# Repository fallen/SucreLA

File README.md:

# SucréLA (READ ONLY, MOVED TO GITLAB)

This is an archived, out-of-date and read-only copy of the SucréLA project.

The project is now hosted on **GitLab** => [https://gitlab.com/yannsionneau/SucreLA](https://gitlab.com/yannsionneau/SucreLA)

## Building

The project Python's dependencies are handled using Pipenv.
However, you must install [nextpnr-ecp5](https://github.com/YosysHQ/nextpnr) and [Yosys](https://github.com/YosysHQ/yosys) if you wish to build the
projet from source.

```
pipenv install --ignore-pipfile
pipenv run python3 ./sucrela.py --build
```

## Flashing the OrangeCrab

```
pipenv run python3 ./sucrela.py --load
```

## Runing simulation

```
pipenv run python3 ./sucrela.py --sim
```

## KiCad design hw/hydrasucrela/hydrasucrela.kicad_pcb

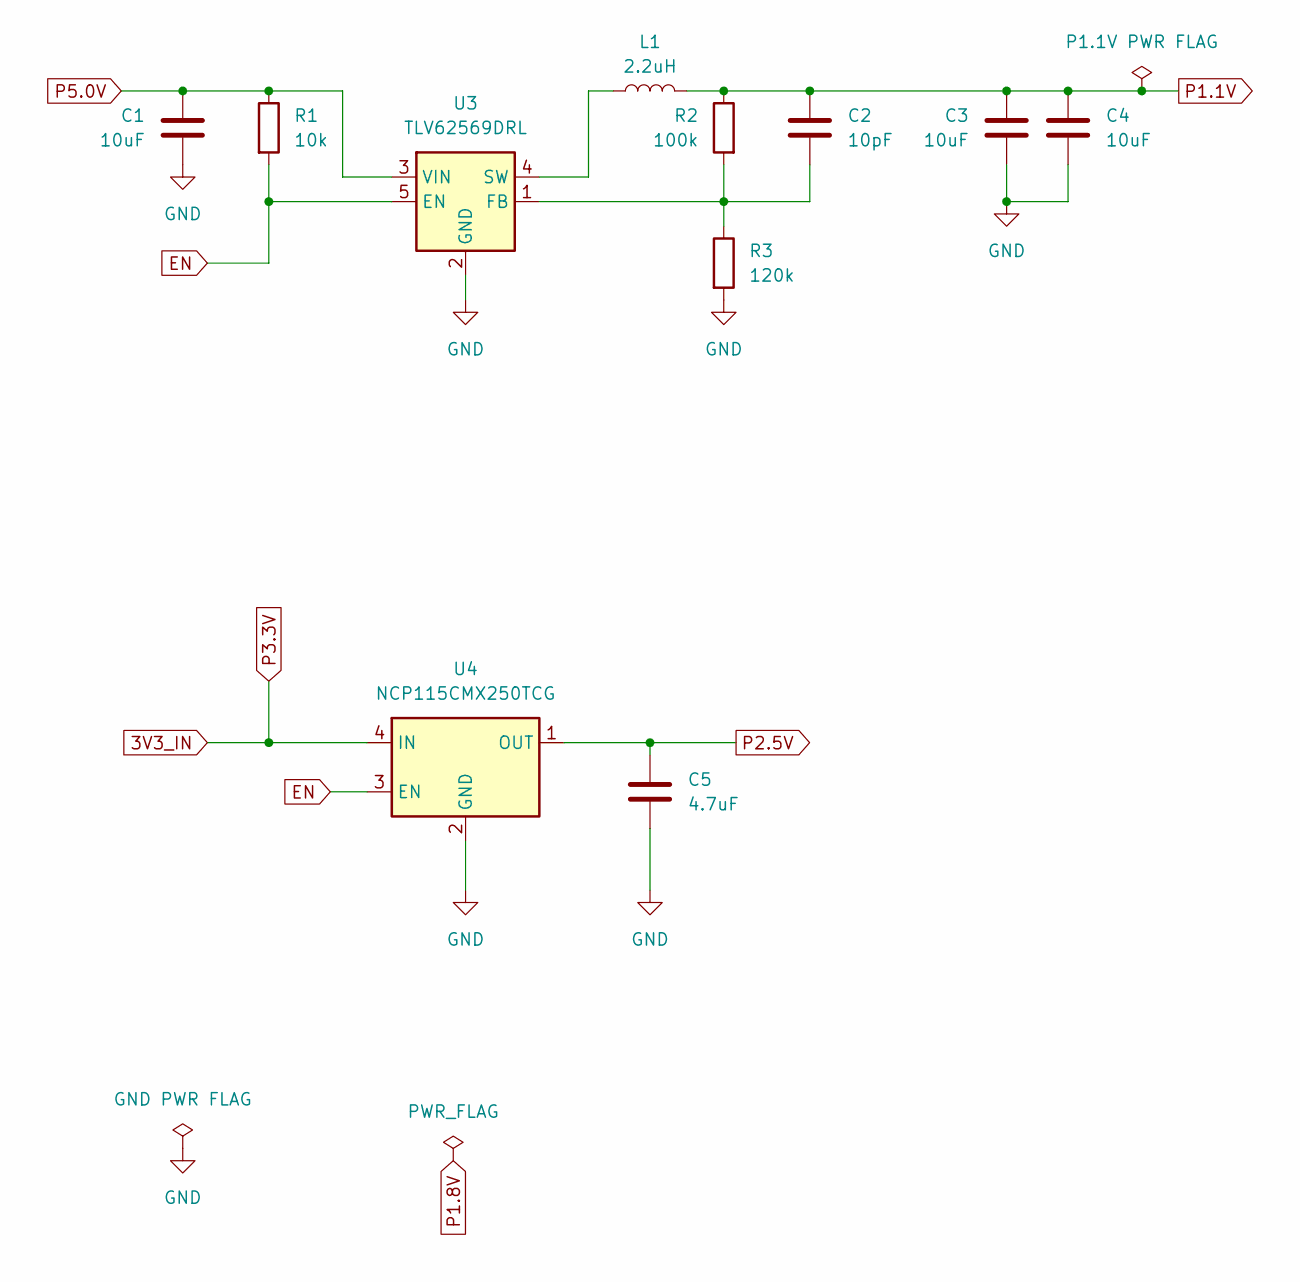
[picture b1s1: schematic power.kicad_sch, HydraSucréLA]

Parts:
C1, C3, C4: 10uF; C_0603_1608Metric_Pad1.08x0.95mm_HandSolder
C2: 10pF; C_0603_1608Metric_Pad1.08x0.95mm_HandSolder
C5: 4.7uF; C_0603_1608Metric_Pad1.08x0.95mm_HandSolder
L1: 2.2uH; L_0603_1608Metric_Pad1.05x0.95mm_HandSolder
R1: 10k; R_0603_1608Metric_Pad0.98x0.95mm_HandSolder
R2: 100k; R_0603_1608Metric_Pad0.98x0.95mm_HandSolder
R3: 120k; R_0603_1608Metric_Pad0.98x0.95mm_HandSolder
U3: TLV62569DRL; SOT-563
U4: NCP115CMX250TCG; OnSemi_XDFN4-1EP_1.0x1.0mm_EP0.52x0.52mm

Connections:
3V3_IN: U4.4 (IN); also elsewhere on the board
EN: R1.2, U3.5 (EN), U4.3 (EN)
GND: C1.2, C3.1, C4.1, C5.2, R3.2, U3.2 (GND), U4.2 (GND), U4.5 (GND); also elsewhere on the board
unnamed: C2.1, R2.2, R3.1, U3.1 (FB)
unnamed: L1.1, U3.4 (SW)
P1.1V: C2.2, C3.2, C4.2, L1.2, R2.1; also elsewhere on the board
P2.5V: C5.1, U4.1 (OUT); also elsewhere on the board
P5.0V: C1.1, R1.1, U3.3 (VIN); also elsewhere on the board

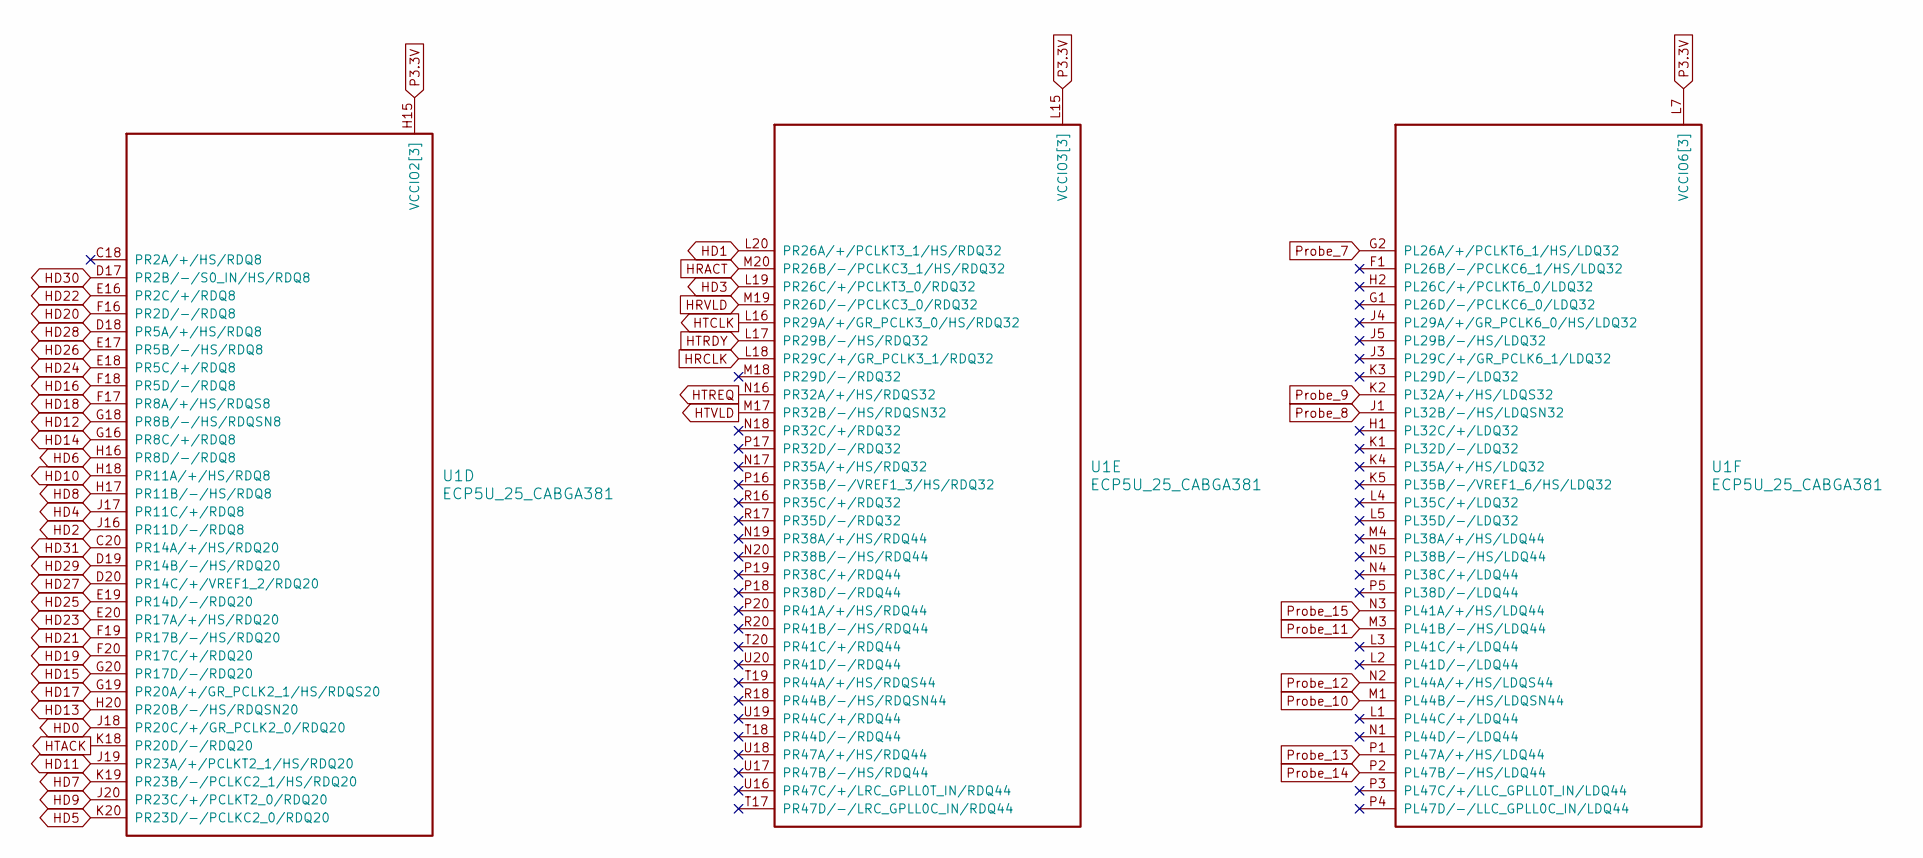
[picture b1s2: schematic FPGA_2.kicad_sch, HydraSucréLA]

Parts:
U1: ECP5U_25_CABGA381; Lattice_caBGA-381_17.0x17.0mm_Layout20x20_P0.8mm_Ball0.4mm_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

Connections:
3V3_IN: U1.H14 (VCCIO2[3]), U1.H15 (VCCIO2[3]), U1.J15 (VCCIO2[3]), U1.L6 (VCCIO6[3]), U1.L7 (VCCIO6[3]), U1.L14 (VCCIO3[3]), U1.L15 (VCCIO3[3]), U1.M6 (VCCIO6[3]), U1.M15 (VCCIO3[3]); also elsewhere on the board
HD0: U1.J18 (PR20C/+/GR_PCLK2_0/RDQ20); also elsewhere on the board
HD1: U1.L20 (PR26A/+/PCLKT3_1/HS/RDQ32); also elsewhere on the board
HD2: U1.J16 (PR11D/-/RDQ8); also elsewhere on the board
HD3: U1.L19 (PR26C/+/PCLKT3_0/RDQ32); also elsewhere on the board
HD4: U1.J17 (PR11C/+/RDQ8); also elsewhere on the board
HD5: U1.K20 (PR23D/-/PCLKC2_0/RDQ20); also elsewhere on the board
HD6: U1.H16 (PR8D/-/RDQ8); also elsewhere on the board
HD7: U1.K19 (PR23B/-/PCLKC2_1/HS/RDQ20); also elsewhere on the board
HD8: U1.H17 (PR11B/-/HS/RDQ8); also elsewhere on the board
HD9: U1.J20 (PR23C/+/PCLKT2_0/RDQ20); also elsewhere on the board
HD10: U1.H18 (PR11A/+/HS/RDQ8); also elsewhere on the board
HD11: U1.J19 (PR23A/+/PCLKT2_1/HS/RDQ20); also elsewhere on the board
HD12: U1.G18 (PR8B/-/HS/RDQSN8); also elsewhere on the board
HD13: U1.H20 (PR20B/-/HS/RDQSN20); also elsewhere on the board
HD14: U1.G16 (PR8C/+/RDQ8); also elsewhere on the board
HD15: U1.G20 (PR17D/-/RDQ20); also elsewhere on the board
HD16: U1.F18 (PR5D/-/RDQ8); also elsewhere on the board
HD17: U1.G19 (PR20A/+/GR_PCLK2_1/HS/RDQS20); also elsewhere on the board
HD18: U1.F17 (PR8A/+/HS/RDQS8); also elsewhere on the board
HD19: U1.F20 (PR17C/+/RDQ20); also elsewhere on the board
HD20: U1.F16 (PR2D/-/RDQ8); also elsewhere on the board
HD21: U1.F19 (PR17B/-/HS/RDQ20); also elsewhere on the board
HD22: U1.E16 (PR2C/+/RDQ8); also elsewhere on the board
HD23: U1.E20 (PR17A/+/HS/RDQ20); also elsewhere on the board
HD24: U1.E18 (PR5C/+/RDQ8); also elsewhere on the board
HD25: U1.E19 (PR14D/-/RDQ20); also elsewhere on the board
HD26: U1.E17 (PR5B/-/HS/RDQ8); also elsewhere on the board
HD27: U1.D20 (PR14C/+/VREF1_2/RDQ20); also elsewhere on the board
HD28: U1.D18 (PR5A/+/HS/RDQ8); also elsewhere on the board
HD29: U1.D19 (PR14B/-/HS/RDQ20); also elsewhere on the board
HD30: U1.D17 (PR2B/-/S0_IN/HS/RDQ8); also elsewhere on the board
HD31: U1.C20 (PR14A/+/HS/RDQ20); also elsewhere on the board
HRACT: U1.M20 (PR26B/-/PCLKC3_1/HS/RDQ32); also elsewhere on the board
HRCLK: U1.L18 (PR29C/+/GR_PCLK3_1/RDQ32); also elsewhere on the board
HRVLD: U1.M19 (PR26D/-/PCLKC3_0/RDQ32); also elsewhere on the board
HTACK: U1.K18 (PR20D/-/RDQ20); also elsewhere on the board
HTCLK: U1.L16 (PR29A/+/GR_PCLK3_0/HS/RDQ32); also elsewhere on the board
HTRDY: U1.L17 (PR29B/-/HS/RDQ32); also elsewhere on the board
HTREQ: U1.N16 (PR32A/+/HS/RDQS32); also elsewhere on the board
HTVLD: U1.M17 (PR32B/-/HS/RDQSN32); also elsewhere on the board
Probe_7: U1.G2 (PL26A/+/PCLKT6_1/HS/LDQ32); also elsewhere on the board
Probe_8: U1.J1 (PL32B/-/HS/LDQSN32); also elsewhere on the board
Probe_9: U1.K2 (PL32A/+/HS/LDQS32); also elsewhere on the board
Probe_10: U1.M1 (PL44B/-/HS/LDQSN44); also elsewhere on the board
Probe_11: U1.M3 (PL41B/-/HS/LDQ44); also elsewhere on the board
Probe_12: U1.N2 (PL44A/+/HS/LDQS44); also elsewhere on the board
Probe_13: U1.P1 (PL47A/+/HS/LDQ44); also elsewhere on the board
Probe_14: U1.P2 (PL47B/-/HS/LDQ44); also elsewhere on the board
Probe_15: U1.N3 (PL41A/+/HS/LDQ44); also elsewhere on the board

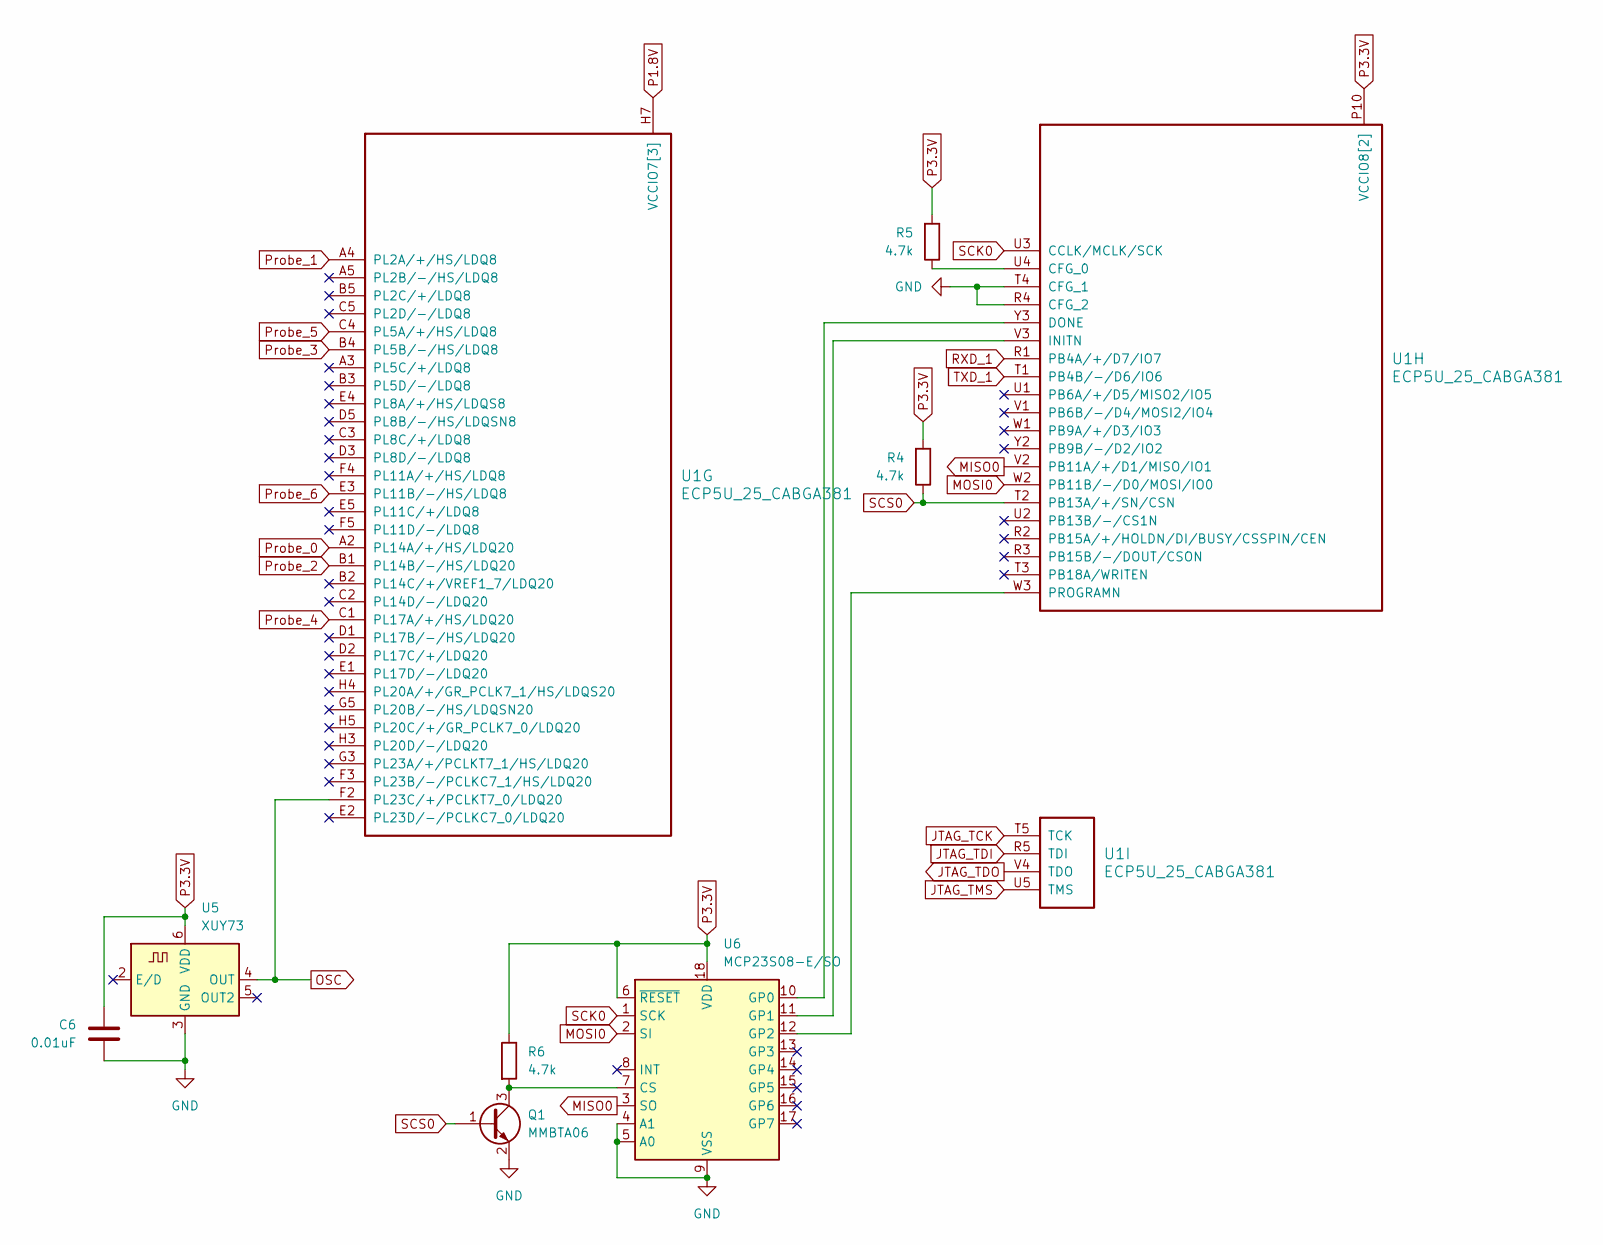
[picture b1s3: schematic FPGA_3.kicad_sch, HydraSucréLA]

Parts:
C6: 0.01uF; C_0603_1608Metric_Pad1.08x0.95mm_HandSolder
Q1: MMBTA06; SOT-23
R4, R5, R6: 4.7k; R_0603_1608Metric_Pad0.98x0.95mm_HandSolder
U1: ECP5U_25_CABGA381; Lattice_caBGA-381_17.0x17.0mm_Layout20x20_P0.8mm_Ball0.4mm_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
U5: XUY73; Oscillator_SMD_IDT_JU6-6_7.0x5.0mm_P2.54mm
U6: MCP23S08-E/SO; SOIC-18W_7.5x11.6mm_P1.27mm

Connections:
3V3_IN: C6.1, R4.2, R5.2, R6.1, U1.P9 (VCCIO8[2]), U1.P10 (VCCIO8[2]), U5.6 (VDD), U6.6 (~RESET), U6.18 (VDD); also elsewhere on the board
GND: C6.2, Q1.2 (E), U1.R4 (CFG_2), U1.T4 (CFG_1), U5.3 (GND), U6.4 (A1), U6.5 (A0), U6.9 (VSS); also elsewhere on the board
JTAG_TCK: U1.T5 (TCK); also elsewhere on the board
JTAG_TDI: U1.R5 (TDI); also elsewhere on the board
JTAG_TDO: U1.V4 (TDO); also elsewhere on the board
JTAG_TMS: U1.U5 (TMS); also elsewhere on the board
MISO0: U1.V2 (PB11A/+/D1/MISO/IO1), U6.3 (SO); also elsewhere on the board
MOSI0: U1.W2 (PB11B/-/D0/MOSI/IO0), U6.2 (SI); also elsewhere on the board
unnamed: Q1.3 (C), R6.2, U6.7 (CS)
unnamed: R5.1, U1.U4 (CFG_0)
unnamed: U1.Y3 (DONE), U6.10 (GP0)
unnamed: U1.V3 (INITN), U6.11 (GP1)
unnamed: U1.W3 (PROGRAMN), U6.12 (GP2)
OSC: U1.F2 (PL23C/+/PCLKT7_0/LDQ20), U5.4 (OUT)
P1.8V: U1.H6 (VCCIO7[3]), U1.H7 (VCCIO7[3]), U1.J6 (VCCIO7[3])
Probe_0: U1.A2 (PL14A/+/HS/LDQ20); also elsewhere on the board
Probe_1: U1.A4 (PL2A/+/HS/LDQ8); also elsewhere on the board
Probe_2: U1.B1 (PL14B/-/HS/LDQ20); also elsewhere on the board
Probe_3: U1.B4 (PL5B/-/HS/LDQ8); also elsewhere on the board
Probe_4: U1.C1 (PL17A/+/HS/LDQ20); also elsewhere on the board
Probe_5: U1.C4 (PL5A/+/HS/LDQ8); also elsewhere on the board
Probe_6: U1.E3 (PL11B/-/HS/LDQ8); also elsewhere on the board
RXD_1: U1.R1 (PB4A/+/D7/IO7); also elsewhere on the board
SCK0: U1.U3 (CCLK/MCLK/SCK), U6.1 (SCK); also elsewhere on the board
SCS0: Q1.1 (B), R4.1, U1.T2 (PB13A/+/SN/CSN); also elsewhere on the board
TXD_1: U1.T1 (PB4B/-/D6/IO6); also elsewhere on the board

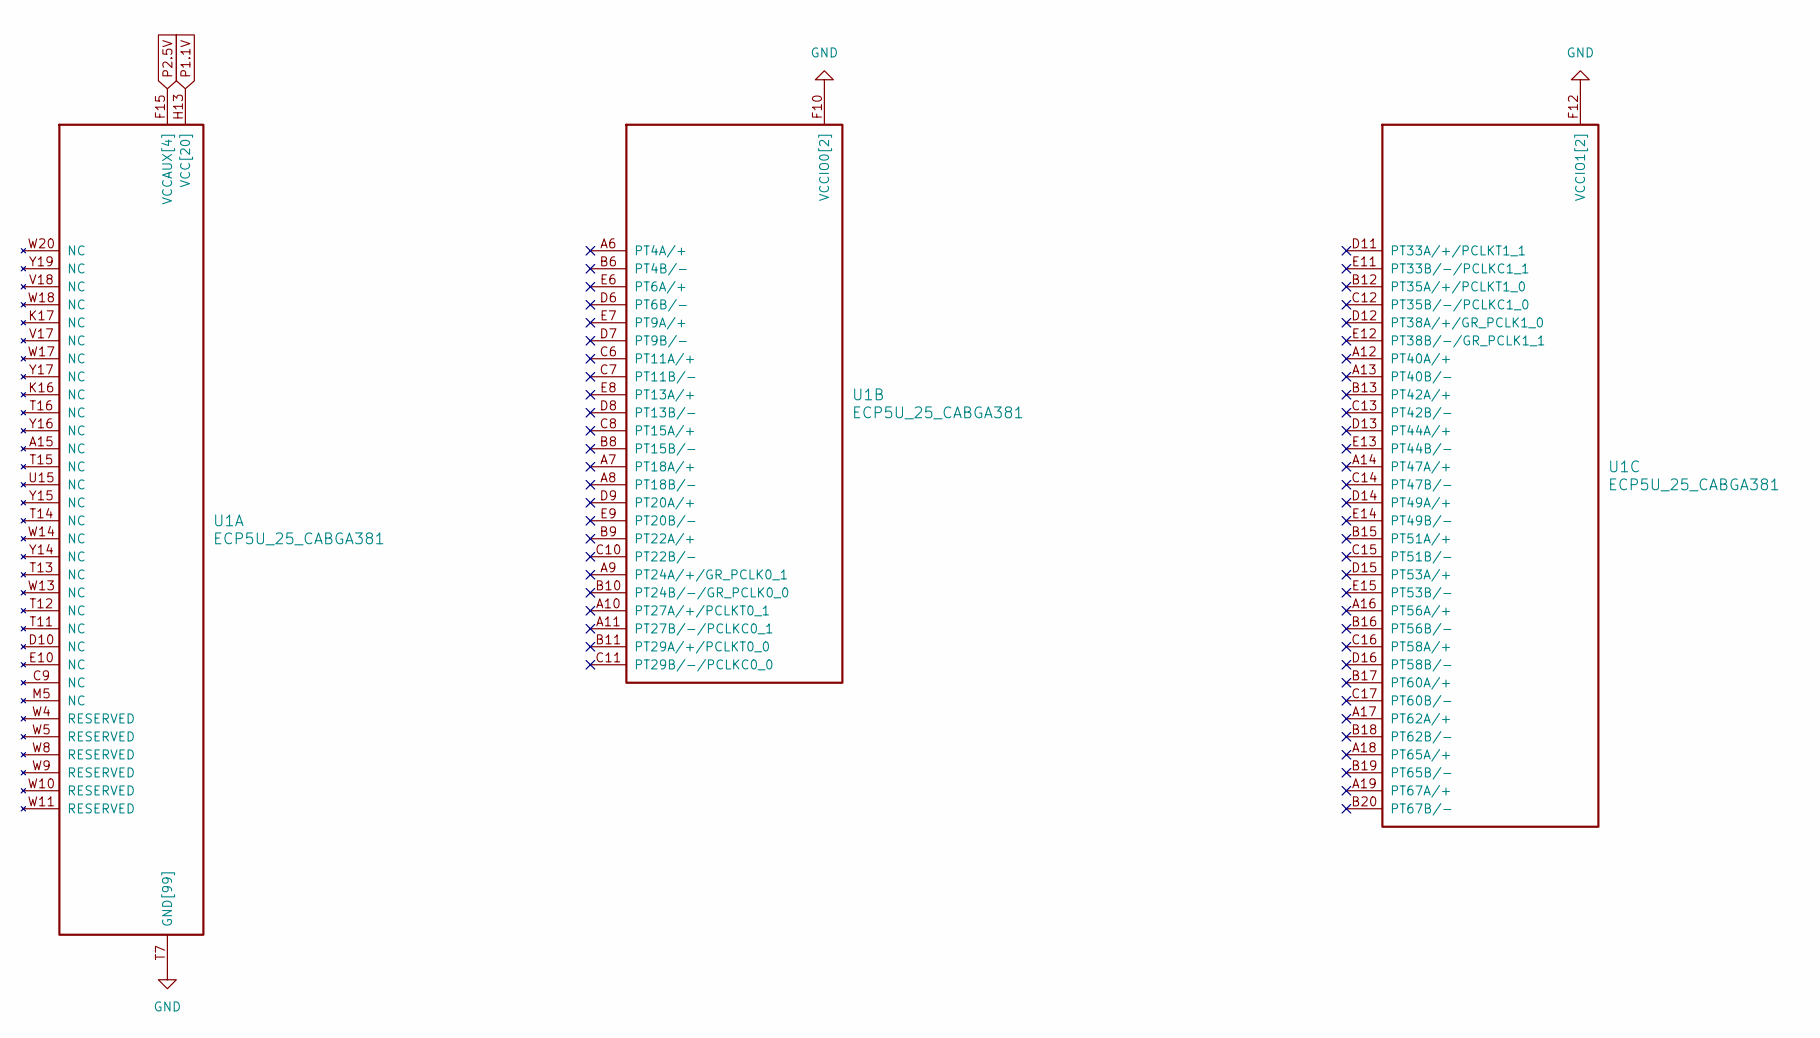
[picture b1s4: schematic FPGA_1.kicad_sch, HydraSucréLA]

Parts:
U1: ECP5U_25_CABGA381; Lattice_caBGA-381_17.0x17.0mm_Layout20x20_P0.8mm_Ball0.4mm_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

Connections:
GND: U1.B7 (GND[99]), U1.B14 (GND[99]), U1.C19 (GND[99]), U1.D4 (GND[99]), U1.F7 (GND[99]), U1.F8 (GND[99]), U1.F9 (VCCIO0[2]), U1.F10 (VCCIO0[2]), U1.F11 (VCCIO1[2]), U1.F12 (VCCIO1[2]), U1.F13 (GND[99]), U1.F14 (GND[99]), U1.G4 (GND[99]), U1.G6 (GND[99]), U1.G7 (GND[99]), U1.G8 (GND[99]), U1.G9 (GND[99]), U1.G10 (GND[99]), U1.G11 (GND[99]), U1.G12 (GND[99]), U1.G13 (GND[99]), U1.G14 (GND[99]), U1.G15 (GND[99]), U1.G17 (GND[99]), U1.H19 (GND[99]), U1.J2 (GND[99]), U1.J7 (GND[99]), U1.J9 (GND[99]), U1.J10 (GND[99]), U1.J11 (GND[99]), U1.J12 (GND[99]), U1.J14 (GND[99]), U1.K6 (GND[99]), U1.K7 (GND[99]), U1.K9 (GND[99]), U1.K10 (GND[99]), U1.K11 (GND[99]), U1.K12 (GND[99]), U1.K14 (GND[99]), U1.K15 (GND[99]), U1.L9 (GND[99]), U1.L10 (GND[99]), U1.L11 (GND[99]), U1.L12 (GND[99]), U1.M2 (GND[99]), U1.M7 (GND[99]), U1.M9 (GND[99]), U1.M10 (GND[99]), U1.M11 (GND[99]), U1.M12 (GND[99]), U1.M14 (GND[99]), U1.M16 (GND[99]), U1.N6 (GND[99]), U1.N7 (GND[99]), U1.N14 (GND[99]), U1.N15 (GND[99]), U1.P7 (GND[99]), U1.P8 (GND[99]), U1.P11 (GND[99]), U1.P12 (GND[99]), U1.P13 (GND[99]), U1.P14 (GND[99]), U1.R19 (GND[99]), U1.T6 (GND[99]), U1.T7 (GND[99]), U1.T8 (GND[99]), U1.T9 (GND[99]), U1.T10 (GND[99]), U1.U6 (GND[99]), U1.U7 (GND[99]), U1.U8 (GND[99]), U1.U9 (GND[99]), U1.U10 (GND[99]), U1.U11 (GND[99]), U1.U12 (GND[99]), U1.U13 (GND[99]), U1.U14 (GND[99]), U1.V5 (GND[99]), U1.V6 (GND[99]), U1.V7 (GND[99]), U1.V8 (GND[99]), U1.V9 (GND[99]), U1.V10 (GND[99]), U1.V11 (GND[99]), U1.V12 (GND[99]), U1.V13 (GND[99]), U1.V14 (GND[99]), U1.V15 (GND[99]), U1.V16 (GND[99]), U1.V19 (GND[99]), U1.V20 (GND[99]), U1.W6 (GND[99]), U1.W7 (GND[99]), U1.W12 (GND[99]), U1.W15 (GND[99]), U1.W16 (GND[99]), U1.W19 (GND[99]), U1.Y5 (GND[99]), U1.Y6 (GND[99]), U1.Y7 (GND[99]), U1.Y8 (GND[99]), U1.Y11 (GND[99]), U1.Y12 (GND[99]); also elsewhere on the board
P1.1V: U1.H8 (VCC[20]), U1.H9 (VCC[20]), U1.H10 (VCC[20]), U1.H11 (VCC[20]), U1.H12 (VCC[20]), U1.H13 (VCC[20]), U1.J8 (VCC[20]), U1.J13 (VCC[20]), U1.K8 (VCC[20]), U1.K13 (VCC[20]), U1.L8 (VCC[20]), U1.L13 (VCC[20]), U1.M8 (VCC[20]), U1.M13 (VCC[20]), U1.N8 (VCC[20]), U1.N9 (VCC[20]), U1.N10 (VCC[20]), U1.N11 (VCC[20]), U1.N12 (VCC[20]), U1.N13 (VCC[20]); also elsewhere on the board
P2.5V: U1.F6 (VCCAUX[4]), U1.F15 (VCCAUX[4]), U1.P6 (VCCAUX[4]), U1.P15 (VCCAUX[4]); also elsewhere on the board

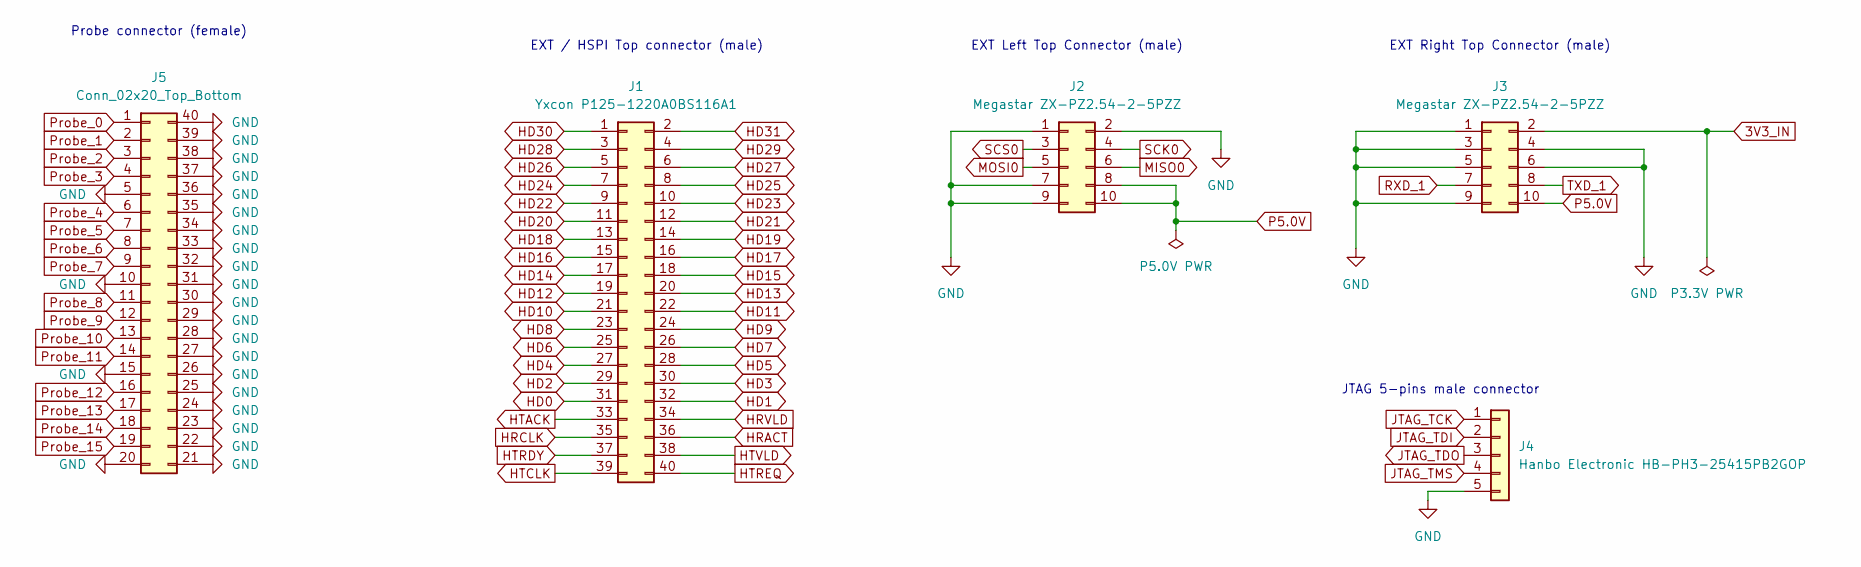
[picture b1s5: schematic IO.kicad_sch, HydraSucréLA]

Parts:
J1: Yxcon P125-1220A0BS116A1; PinHeader_2x20_P2.54mm_Vertical
J2, J3: Megastar ZX-PZ2.54-2-5PZZ; PinHeader_2x05_P2.54mm_Vertical
J4: Hanbo Electronic HB-PH3-25415PB2GOP; PinSocket_1x05_P2.54mm_Vertical
J5: Conn_02x20_Top_Bottom; probe_connector

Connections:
3V3_IN: J3.2; also elsewhere on the board
GND: J2.1, J2.2, J2.7, J2.9, J3.1, J3.3, J3.4, J3.5, J3.6, J3.9, J4.5, J5.5, J5.10, J5.15, J5.20, J5.21, J5.22, J5.23, J5.24, J5.25, J5.26, J5.27, J5.28, J5.29, J5.30, J5.31, J5.32, J5.33, J5.34, J5.35, J5.36, J5.37, J5.38, J5.39, J5.40; also elsewhere on the board
HD0: J1.31; also elsewhere on the board
HD1: J1.32; also elsewhere on the board
HD2: J1.29; also elsewhere on the board
HD3: J1.30; also elsewhere on the board
HD4: J1.27; also elsewhere on the board
HD5: J1.28; also elsewhere on the board
HD6: J1.25; also elsewhere on the board
HD7: J1.26; also elsewhere on the board
HD8: J1.23; also elsewhere on the board
HD9: J1.24; also elsewhere on the board
HD10: J1.21; also elsewhere on the board
HD11: J1.22; also elsewhere on the board
HD12: J1.19; also elsewhere on the board
HD13: J1.20; also elsewhere on the board
HD14: J1.17; also elsewhere on the board
HD15: J1.18; also elsewhere on the board
HD16: J1.15; also elsewhere on the board
HD17: J1.16; also elsewhere on the board
HD18: J1.13; also elsewhere on the board
HD19: J1.14; also elsewhere on the board
HD20: J1.11; also elsewhere on the board
HD21: J1.12; also elsewhere on the board
HD22: J1.9; also elsewhere on the board
HD23: J1.10; also elsewhere on the board
HD24: J1.7; also elsewhere on the board
HD25: J1.8; also elsewhere on the board
HD26: J1.5; also elsewhere on the board
HD27: J1.6; also elsewhere on the board
HD28: J1.3; also elsewhere on the board
HD29: J1.4; also elsewhere on the board
HD30: J1.1; also elsewhere on the board
HD31: J1.2; also elsewhere on the board
HRACT: J1.36; also elsewhere on the board
HRCLK: J1.35; also elsewhere on the board
HRVLD: J1.34; also elsewhere on the board
HTACK: J1.33; also elsewhere on the board
HTCLK: J1.39; also elsewhere on the board
HTRDY: J1.37; also elsewhere on the board
HTREQ: J1.40; also elsewhere on the board
HTVLD: J1.38; also elsewhere on the board
JTAG_TCK: J4.1; also elsewhere on the board
JTAG_TDI: J4.2; also elsewhere on the board
JTAG_TDO: J4.3; also elsewhere on the board
JTAG_TMS: J4.4; also elsewhere on the board
MISO0: J2.6; also elsewhere on the board
MOSI0: J2.5; also elsewhere on the board
P5.0V: J2.8, J2.10, J3.10; also elsewhere on the board
Probe_0: J5.1; also elsewhere on the board
Probe_1: J5.2; also elsewhere on the board
Probe_2: J5.3; also elsewhere on the board
Probe_3: J5.4; also elsewhere on the board
Probe_4: J5.6; also elsewhere on the board
Probe_5: J5.7; also elsewhere on the board
Probe_6: J5.8; also elsewhere on the board
Probe_7: J5.9; also elsewhere on the board
Probe_8: J5.11; also elsewhere on the board
Probe_9: J5.12; also elsewhere on the board
Probe_10: J5.13; also elsewhere on the board
Probe_11: J5.14; also elsewhere on the board
Probe_12: J5.16; also elsewhere on the board
Probe_13: J5.17; also elsewhere on the board
Probe_14: J5.18; also elsewhere on the board
Probe_15: J5.19; also elsewhere on the board
RXD_1: J3.7; also elsewhere on the board
SCK0: J2.4; also elsewhere on the board
SCS0: J2.3; also elsewhere on the board
TXD_1: J3.8; also elsewhere on the board

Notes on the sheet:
Probe connector (female)
EXT Right Top Connector (male)
EXT / HSPI Top connector (male)
JTAG 5-pins male connector
EXT Left Top Connector (male)

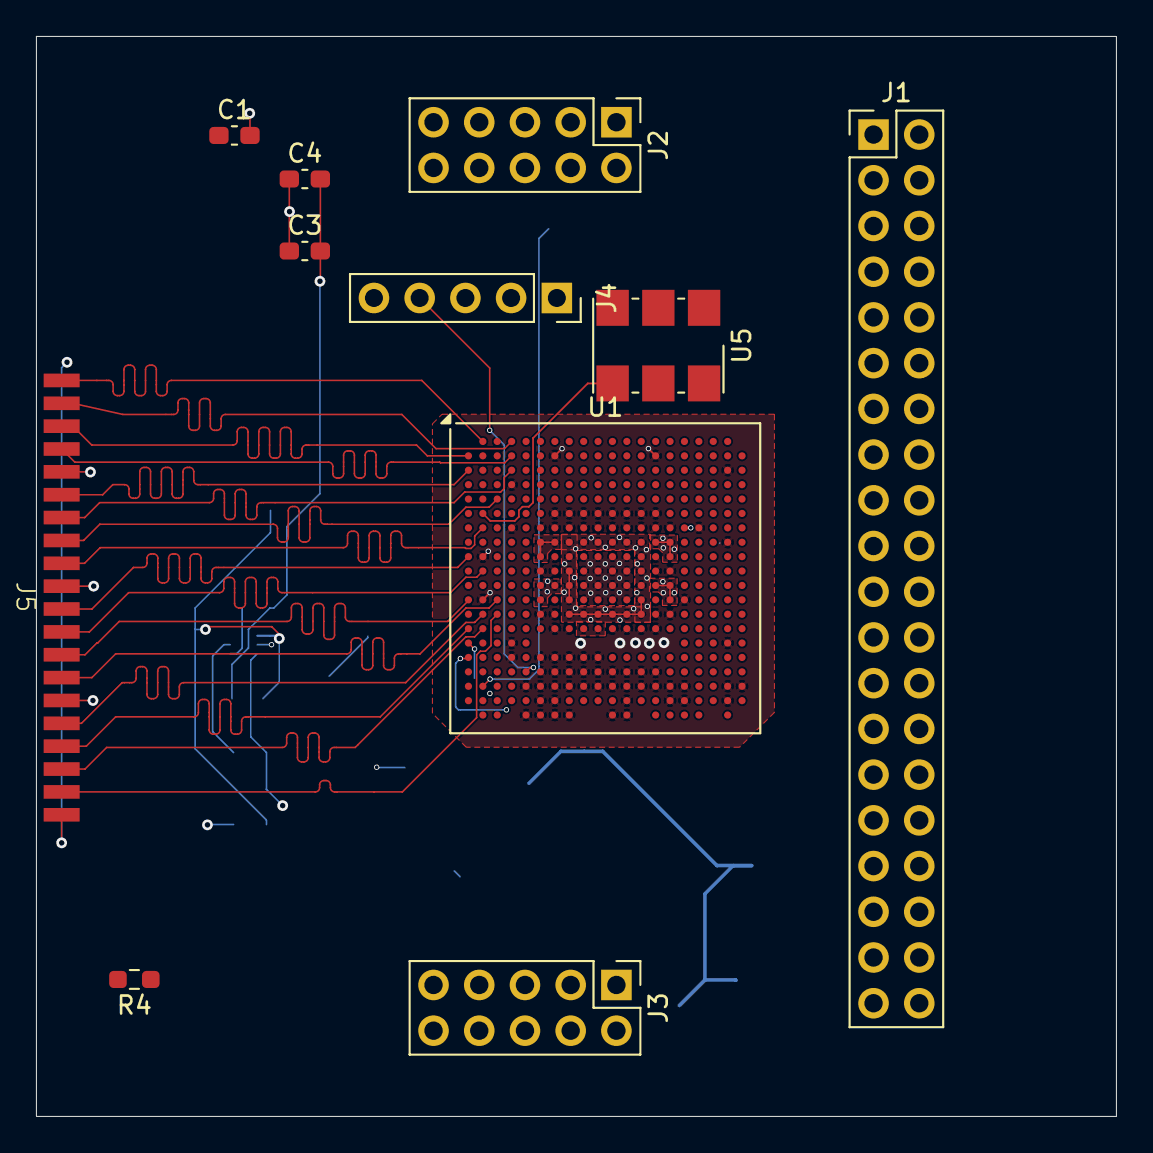
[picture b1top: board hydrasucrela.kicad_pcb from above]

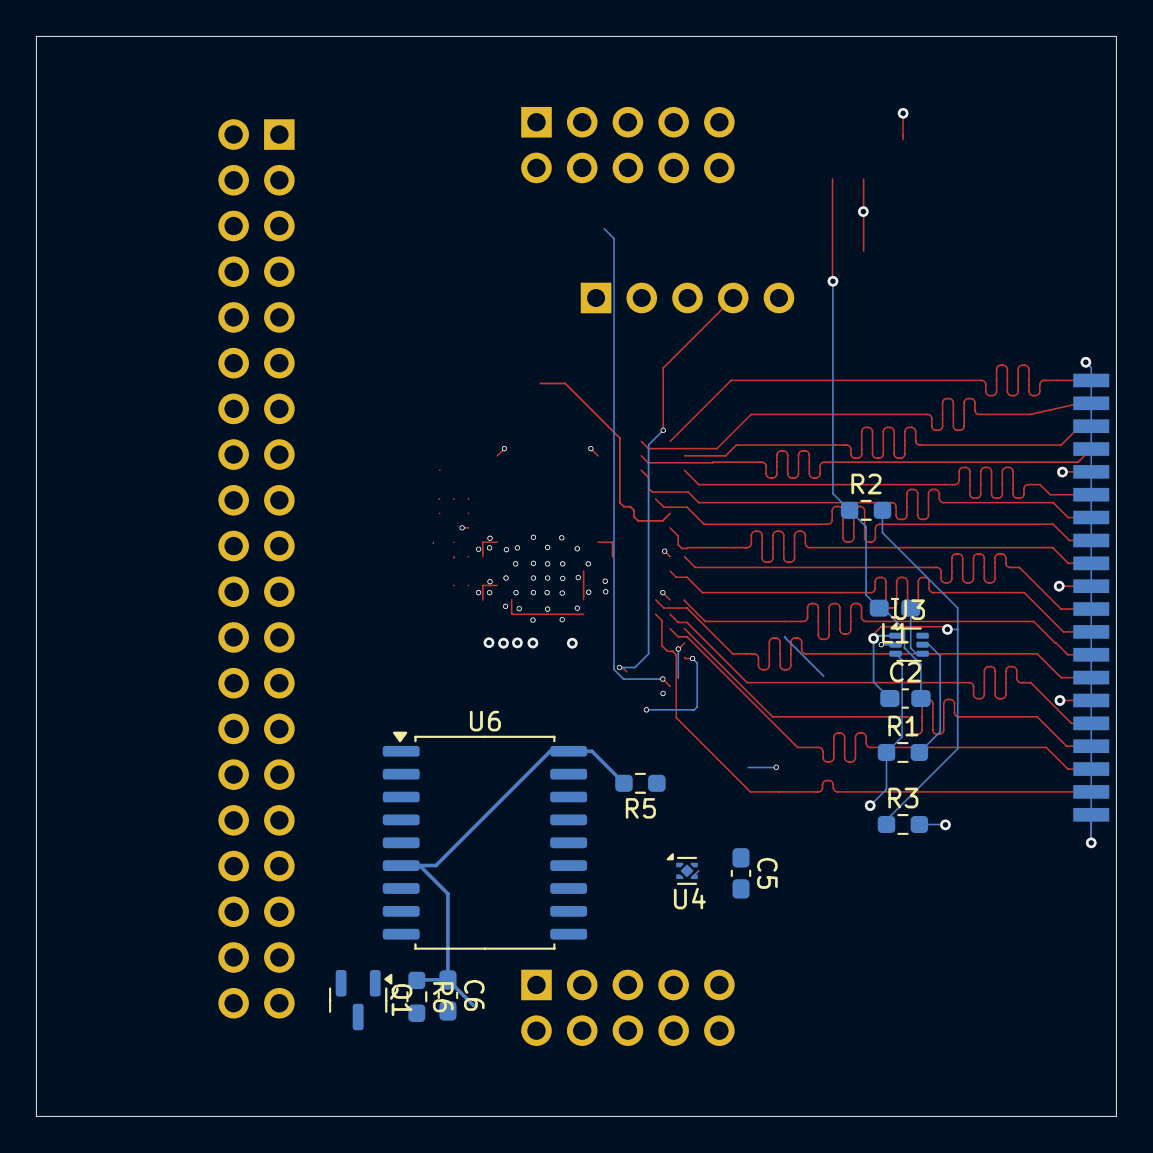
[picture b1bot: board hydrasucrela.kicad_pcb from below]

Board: 4 copper layers, 60.0 x 60.0 mm, 24 parts (13 on the bottom side), 81 nets.

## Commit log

2023-12-15 Build in CI
2023-12-24 Add uartbone client for Linux platform
2023-12-27 uartbone: add -h arg and compile+run it in CI
    -h prints usage/help and returns 0 (success).
    In CI so far we just compile the Linux CLI and runs it with -h
2024-01-09 uartbone: fix print_usage()
2024-01-09 sucrela: refactor pin names and make ECP5 85F the default target
2024-03-03 Add wch CH569 BSP as submodule
2024-03-03 uartbone: put linux specific code out of uartbone.c
    To allow compiling uartbone.c with a bare-metal RISC-V toolchain.
2024-03-03 uartbone: define endianness functions for xpack risc-v newlib nano based toolchain
2024-03-03 Add basic fw for hydrausb3
    HydraUSB3 board is used to prototype SucreLA
    Eventually a board featuring an ECP5 FPGA and a WCH569
    microcontroller will be designed.
    For now, let's use OrangeCrab FPGA board connected to
    HydraUSB3.
2024-03-03 HSPI TX: fixed CRC generation, now it works in simulation
2024-03-03 HSPI TX: make the test really fail the CI if CRC is invalid
2024-03-03 CI: run simulation tests in CI
2024-03-04 CI: Add build step of the HydraUSB3 fw
2024-03-04 fw: fix warning about implicite abort() declaration
2024-03-11 build: generate/use csr.h containing FPGA SoC registers in HydraUSB3 fw
2024-03-11 uartbone: use SendString instead of SendByte
    Because the latter checks if the TX FIFO is full before
    writing to the uart tx register.
2024-03-11 SoC: add comments to avoid back and forth with pinout/schematics pages
2024-03-11 SoC: pass correct arguments from cmdline to SoC constructor
2024-03-11 fw: add working HSPI transfer
    * Also, use CSR regs addresses from csr.h to avoid
    hard-coded addresses.
    * Increase system frequency to 30 MHz
2024-03-15 uartbone: refactor backend callbacks to prepare for USB backend
    USB Bulk will be sent by strings and not byte-by-byte.
    Thus let's use a buffer/len API instead of just a byte based API.
2024-03-15 Update BSP to use new UART rx functions
2024-03-23 libuartbone: make uart_read return error code upon error
2024-03-23 libuartbone: add support for uartbone over USB to Linux CLI
2024-03-23 CI: install libusb before building host tools
2024-03-23 fw: add support for building the usb stack
2024-03-23 fw: boost CPU freq from 30 MHz to 120 MHz
2024-03-23 fw: add support for uartbone over USB
    Host tool can now send USB commands to CH569
    to ask it to send uartbone commands to FPGA SoC.
2024-03-23 bsp: update usb stack
2024-03-23 fw: add missing files for USB
2024-03-23 fw: allocate hspi dma buffers in RAMX via the linker instead of hard coded macros
2024-03-25 CI: update to actions/checkout@v4 because of the Node20 warning
2024-03-25 Improve libuartbone Makefile by using implicit rules
    Also produce a real shared lib named libuartbone.so
2024-03-25 libuartbone: move get_reg_addr into the lib
2024-04-13 HSPI: lots of fix, cleanup and debug
    * Add lots of CSR for debug
    * Wrap all module instances with ClockDomainRenamer to allow design
    simulation in CI
    * it also allows to use a specific "HSPI" clock domain for the LA
    to reduce clock speed from 48 MHz to 4 MHz for the low speed
    prototype.
2024-04-13 Improve LA pipeline
    * Add converter and hspi packet buffer
    This allows to have smaller probe number than
    HSPI bus width.
    This also allows to run sampling and HSPI at same
    speed, because otherwise since HSPI has approx 10 bytes
    overhead (4 bytes header + 2 or 4 bytes CRC + negociation)
2024-04-13 SucreLA: add support for testing mode in top level
    * testing mode inject dummy data
    * it also enables litescope inside the SoC to help debug
    on FPGA.
    * Run the LA at 4 MHz to avoid signal integrity issues with
    flying wires of the prototype.
2024-04-13 mcu: remove discarded qualifiers warning
2024-04-13 mcu: cleanup, remove dead code, make hspi and uartbone work
    now mcu code only acts as bridge between Host PC and FPGA for
    uartbone protocole like this:
    {PC} <=usb EP1=> {MCU} <=uart=> {FPGA [uartbone_bridge] <=> [LiteX wishbone SoC bus] <=> [LogicAnalyzer cores]}
    It also acts as bridge for sample data like this:
    {PC} <=usb EP2=> {MCU} <=HSPI=> {FPGA [LogicAnalyzer HSPI TX] <= [LA Pipeline]}
2024-04-13 libuartbone: allow to init context with libusb device handle already open
    Either call uartbone_unix_init with no libusb device handle with
    file = "usb://vendor:product/EP"
    or if you already have an open libusb handle call uartbone_unix_init
    with
    file = "usb://"
    And don't forget to set those uartbone_ctx fields:
2024-04-13 wch bsp: update to use new usb code
2024-04-13 Add missing config.h
2024-04-14 libsigrok: add libsigrok with SucréLA support as submodule
2024-04-14 CI: build libsigrok with SucréLA support
2024-09-17 hw: add hydrasucrela daughter board design files
2024-09-17 hw: update kicad footprints and symbols
2024-12-15 Update HydraSucreLA PCB
2024-12-16 update PCB with good connector placements
2025-04-12 We moved to GitLab !
    there we are => https://gitlab.com/yannsionneau/SucreLA
